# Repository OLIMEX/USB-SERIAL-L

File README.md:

# USB-SERIAL-L
USB-SERIA-L is the ultimate Open Source Hardware USB to Serial converter with ful modem signals, supporting serial speeds from 100bps up to 3Mbps and with adjustable voltage levels from 0.65V up to 5V

https://www.olimex.com/Products/USB-Modules/USB-SERIAL-L/

## Licensee
* Hardware is released under CERN Open Hardware Licence Version 2 - Strongly Reciprocal
* Software is released under GPL V3 Licensee
* Documentation is released under CC BY-SA 4.0

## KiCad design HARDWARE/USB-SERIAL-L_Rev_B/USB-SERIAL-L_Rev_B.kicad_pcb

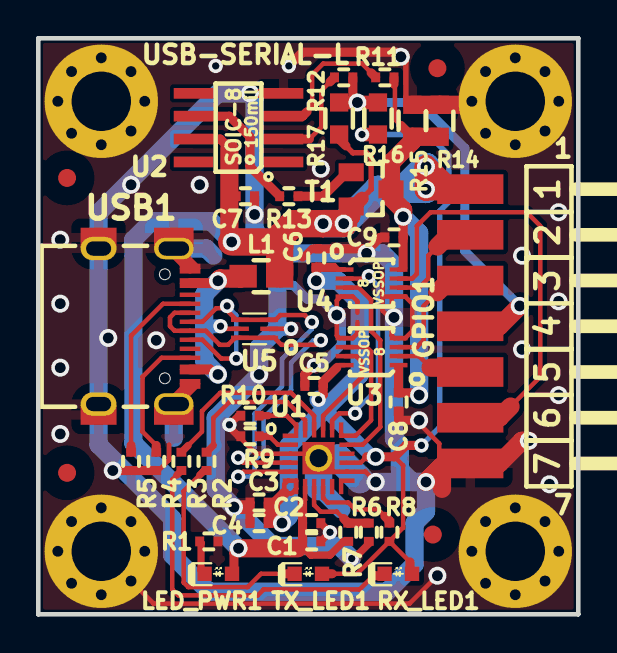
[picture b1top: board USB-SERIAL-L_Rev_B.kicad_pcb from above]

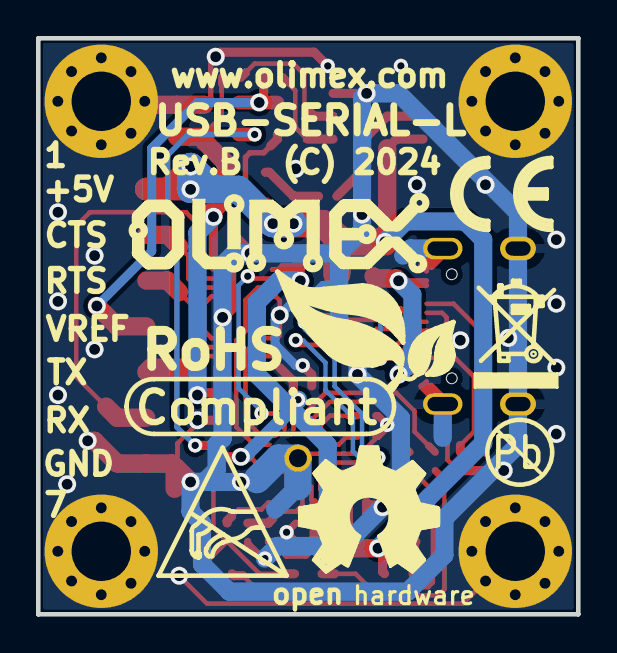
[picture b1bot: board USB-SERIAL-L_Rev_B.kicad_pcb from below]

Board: 2 copper layers, 30.0 x 32.0 mm, 53 parts (7 on the bottom side), 31 nets.

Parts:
C1, C3: 4.7uF/X5R/20%/10V/C0402; C_0402_5MIL_DWS
C2, C4, C5, C6, C7, C8, C9: 100nF/10V/20%/X5R/C0402; C_0402_5MIL_DWS
FID1, FID2: Fiducial; Fiducial1x3
FID3, FID4: Fiducial; Fiducial1x3_Paste
GPIO1: HN1x7(SMD)_H-WX-1x7-LF
L1: IND/600OHM/2A/UPZ2012E-601-2R0TF/L0805; L_0805_5MIL_DWS
LED_PWR1: LED/YELLOW/0603; LED_0603_KA
Logo_OLIMEX_TB-Bottom: Logo_OLIMEX_TB
Mount-Hole-3.3mm1, Mount-Hole-3.3mm2, Mount-Hole-3.3mm3, Mount-Hole-3.3mm4: Mounting_hole_Shield_3.3mm
R1, R2, R3: 2.2k/R0402; R_0402_5MIL_DWS
R4, R5: 5.1k/1%/R0402; R_0402_5MIL_DWS
R6: 10k/1%/R0402; R_0402_5MIL_DWS
R7: 4.7K/1%/R0402; R_0402_5MIL_DWS
R8, R11, R12, R13: 1k/R0402; R_0402_5MIL_DWS
R9, R10: 10k/R0402; R_0402_5MIL_DWS
R14, R15: 300R/R0603/5%; R_0603_5MIL_DWS
R16: 22K/R0603; R_0603_5MIL_DWS
R17: NA(22K/R0603); R_0603_5MIL_DWS
RX_LED1: LED/RED/0603; LED_0603_KA
Sign_Antistatic: Sign_Antistatic
Sign_CE: CE_Sign
Sign_OSHW_8x8: Sign_OSHW_8x8
Sign_PB-Free: Sign_PB-Free
Sign_RecycleBin: Sign_RecycleBin; Sign_RecycleBin_1
Sign_RoHS: Sign_RoHS; Sign_RoHS_1
T1: BC807-40/PNP/SOT23; SOT23
TX_LED1: LED/GREEN/0603; LED_0603_KA
U1: CP2102N-QFN20; QFN-20-1EP_3x3mm_P0.5mm_EP1.8x1.8mm
U2: MCP6041-I/SN; SOIC-8_150mil
U3, U4: SN74AXC2T45DCUR; VSSOP-8_Pitch-0.50mm_Pad-0.25mm_Dimensions-2.30x2.00x1.00mm
U5: USBLC6-2P6; SOT-666
USB1: USB-C-16P-F(A40-00119-A52-12); USB2.0_TYPE-C(A40-00119-A52-12)_Paste

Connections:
+3.3V: C3.1, C4.1, C5.1, C6.1, R8.2, R16.2, RX_LED1.2 (A), TX_LED1.2 (A), U1.6 (VDD), U1.13 (~WAKEUP), U3.8 (VCCB), U4.1 (VCCA)
+5V_USB: C1.1, C2.1, C7.1, GPIO1.1, L1.2, LED_PWR1.2 (A), R7.2, R17.2, T1.2 (E), U1.7 (VREGIN), U2.7 (V+)
/CTS: GPIO1.2, U4.6 (B2)
/CTS_3V3: U1.15 (~CTS), U4.3 (A2)
/D+: U1.4 (D+), U5.3 (I/O2), U5.4 (I/O2), USB1.A6 (DP1), USB1.B6 (DP2)
/D-: U1.5 (D-), U5.1 (I/O1), U5.6 (I/O1), USB1.A7 (DN1), USB1.B7 (DN2)
/RTS: GPIO1.3, U3.3 (A2)
/RTS_3V3: U1.16 (~RTS), U3.6 (B2)
/RX: GPIO1.6, U4.7 (B1)
/RX_3V3: U1.17 (RXD), U4.2 (A1)
/RX_LED: R3.2, U1.19 (~RXT/GPIO3)
/TX: GPIO1.5, U3.2 (A1)
/TX_3V3: U1.18 (TXD), U3.7 (B1)
/TX_LED: R2.2, U1.20 (~TXT/GPIO2)
/VREF: GPIO1.4, R12.1, R16.1, R17.1
GND: C1.2, C2.2, C3.2, C4.2, C5.2, C6.2, C7.2, C8.2, C9.2, GPIO1.7, Mount-Hole-3.3mm1.GND1, Mount-Hole-3.3mm2.GND1, Mount-Hole-3.3mm3.GND1, Mount-Hole-3.3mm4.GND1, R1.2, R4.1, R5.1, R6.2, R9.2, R10.2, R14.2, R15.2, U1.3 (GND), U1.12 (GND), U1.21 (GND), U2.4 (GND), U3.4 (GND), U3.5 (DIR), U4.4 (GND), U4.5 (DIR), U5.2 (GND), USB1.0 (SHELL), USB1.A1 (GND), USB1.A12 (GND), USB1.B1 (GND), USB1.B12 (GND)
unnamed: LED_PWR1.1 (K), R1.1
unnamed: R3.1, RX_LED1.1 (K)
unnamed: R13.2, T1.1 (B)
unnamed: C8.1, C9.1, R11.1, R14.1, R15.1, T1.3 (C), U3.1 (VCCA), U4.8 (VCCB)
unnamed: R2.1, TX_LED1.1 (K)
unnamed: R9.1, U1.2 (CLK/GPIO0)
unnamed: R10.1, U1.1 (RS485/GPIO1)
unnamed: R6.1, R7.1, U1.8 (VBUS)
unnamed: R8.1, U1.9 (~RST)
unnamed: R11.2, U2.3 (+IN)
unnamed: R12.2, U2.2 (-IN)
unnamed: R13.1, U2.6 (VOUT)
unnamed: L1.1, U5.5 (VBUS), USB1.A4 (VBUS), USB1.A9 (VBUS), USB1.B4 (VBUS), USB1.B9 (VBUS)
unnamed: R5.2, USB1.A5 (CC1)
unnamed: R4.2, USB1.B5 (CC2)

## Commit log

2024-10-18 initial upload
2024-11-28 user manual

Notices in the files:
HARDWARE/USB-SERIAL-L_Rev_B/USB-SERIAL-L_Rev_B.kicad_pcb:
(C) 2024
